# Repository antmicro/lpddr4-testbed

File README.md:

LPDDR4 testbed
==============

Copyright (c) 2020-2025 [Antmicro](https://www.antmicro.com)

Overview
--------

This repository contains open hardware design files for an experimental
test module in a form of SO-DIMM DDR4 module. The module includes a
standard 200-ball WFBGA (10mm × 14.5mm × 0.8mm, Ø0.35 SMD) LPDDR4 RAM
footprint break-routed in the SO-DOMM edge connector. The design files
were prepared in KiCad. Please note that this board is not electrically
compatible with off-the-shelf SO-DIMM DDR4 memory modules. It is
compatible with [this](https://github.com/antmicro/lpddr4-test-board)
LPDDR4 test platform.

Repository structure
--------------------

The main repository directory contains KiCad PCB project files, a
LICENSE and README. The remaining files are stored in the following
directories:

* `img` - contains graphics for this README

### Licensing

This project is published under the [Apache-2.0](LICENSE) license.

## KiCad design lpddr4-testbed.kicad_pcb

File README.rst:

==============
LPDDR4 testbed
==============

Copyright (c) 2020-2021 `Antmicro <https://www.antmicro.com>`_

.. figure:: img/lpddr4-testbed.jpg

Overview
--------

This repository contains open hardware design files for an experimental test module in a form of SO-DIMM DDR4 module. The module includes a standard 200-ball WFBGA (10mm × 14.5mm ×
0.8mm, Ø0.35 SMD) LPDDR4 RAM footprint break-routed in the SO-DOMM edge connector.
The design files were prepared in KiCad.
Please note that this board is not electrically compatible with off-the-shelf SO-DIMM DDR4 memory modules.
It is compatible with `this <https://github.com/antmicro/lpddr4-test-board>`_ LPDDR4 test platform.

Repository structure
--------------------
The main repository directory contains KiCad PCB project files, a LICENSE and README.
The remaining files are stored in the following directories:

* ``lib`` - contains the component libraries
* ``img`` - contains graphics for this README

License
=======

`Apache-2.0 <LICENSE>`_

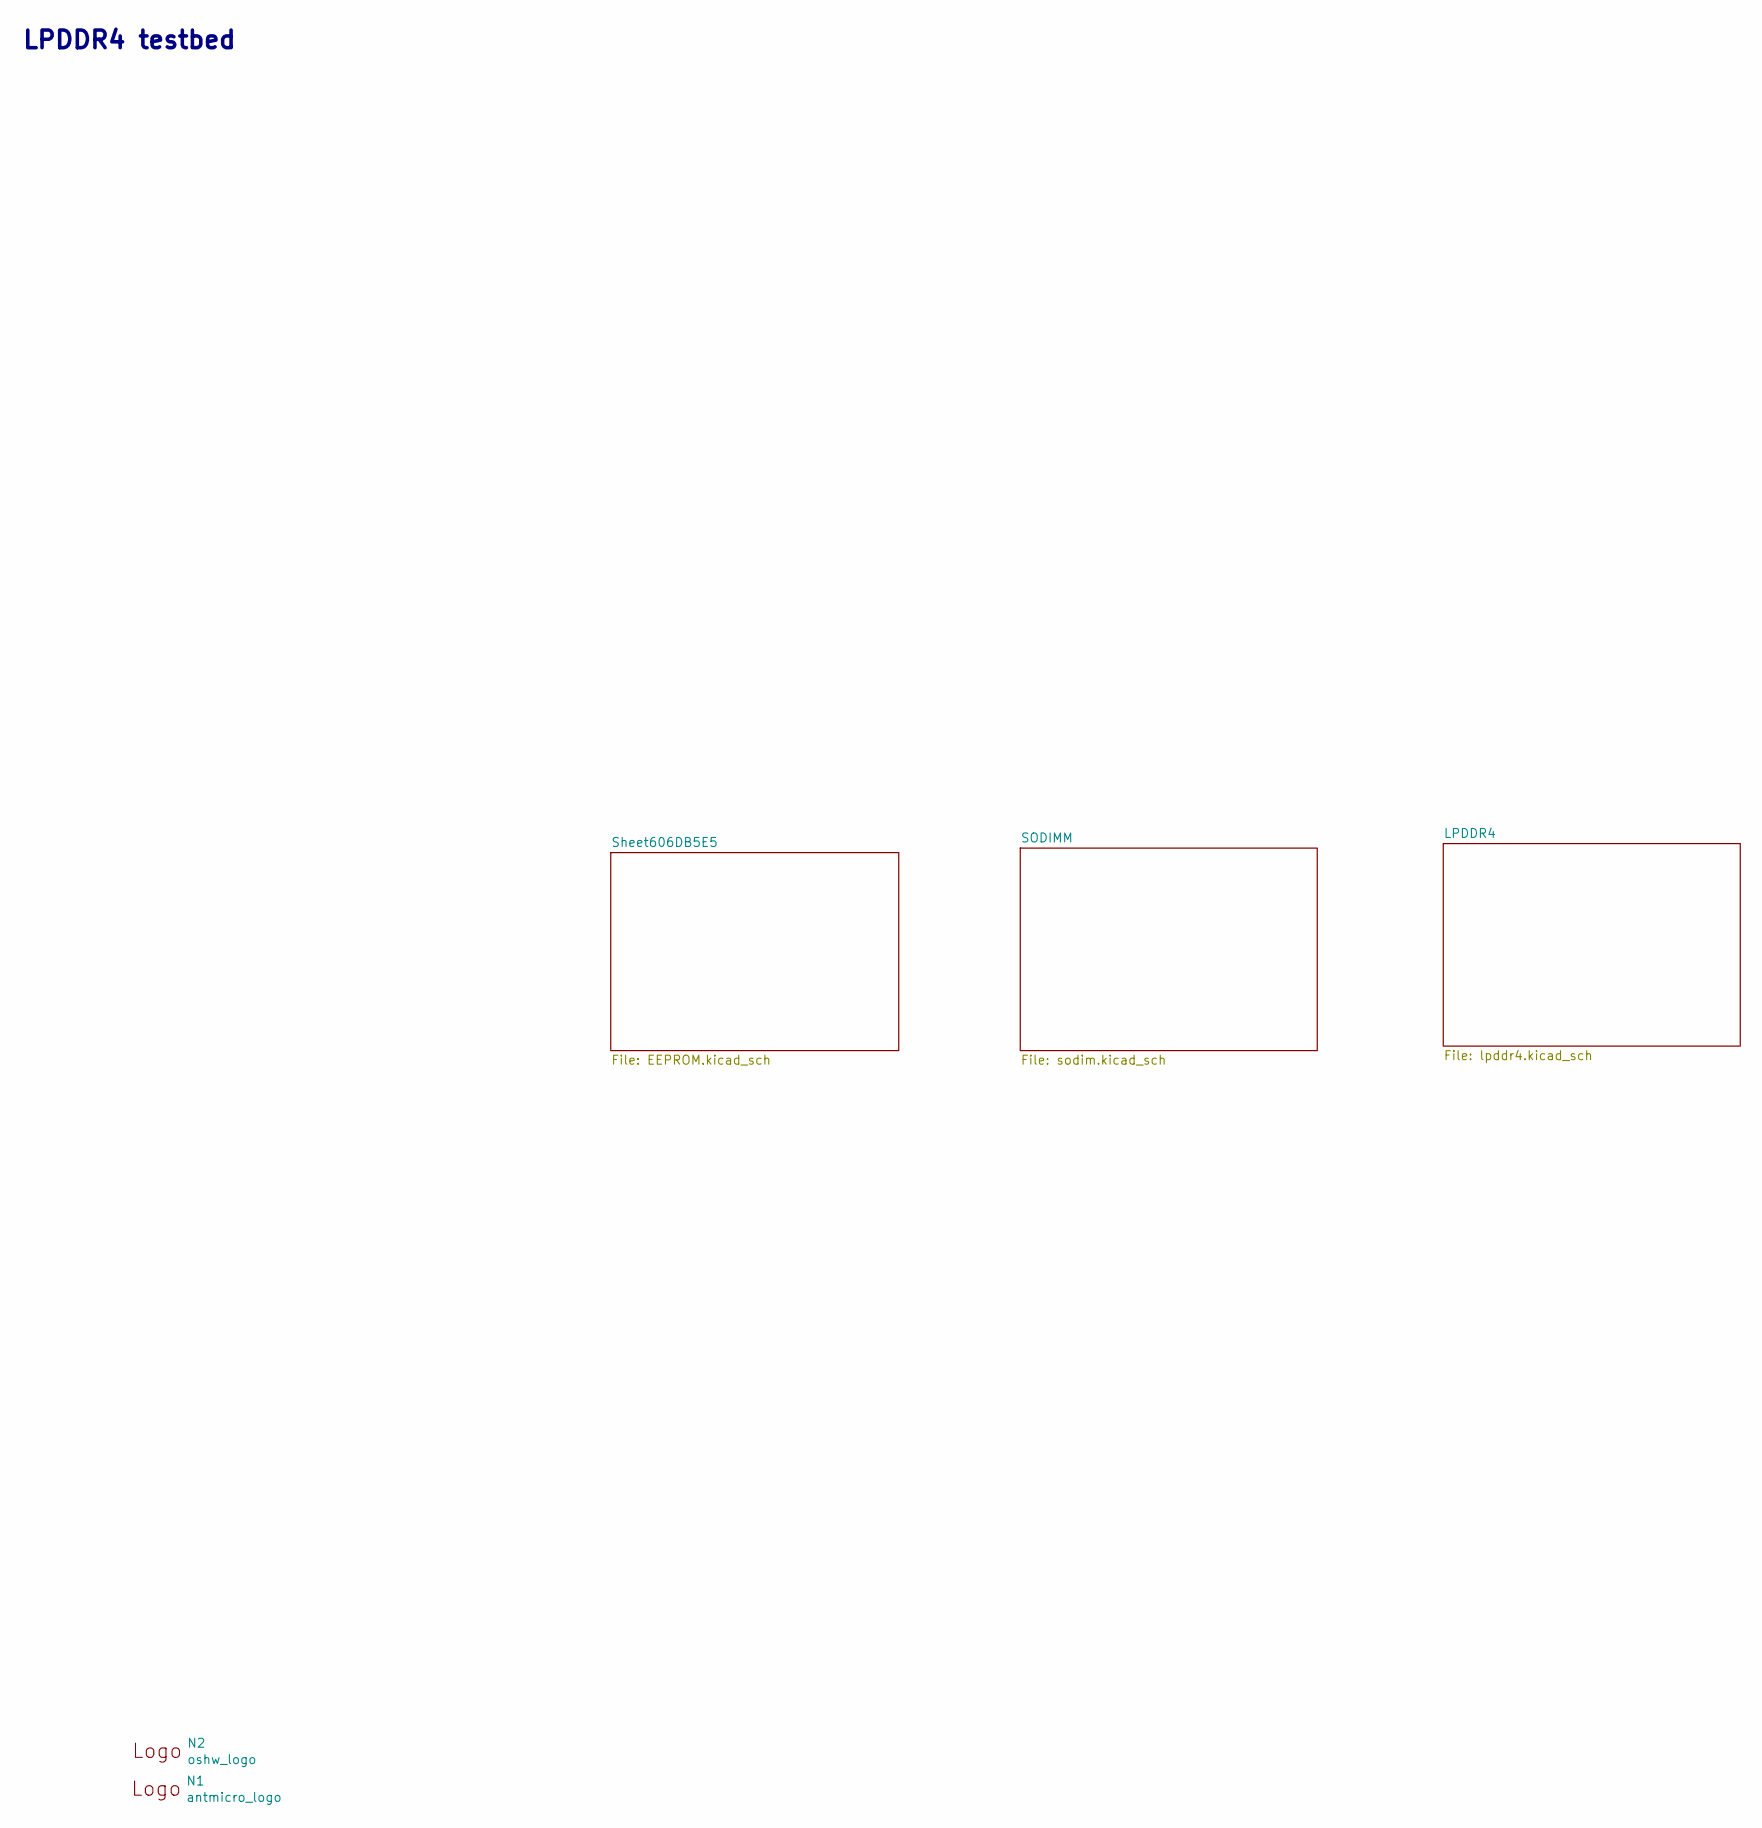
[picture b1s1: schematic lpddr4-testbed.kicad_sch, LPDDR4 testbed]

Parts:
N1: antmicro_logo; antmicro-logo_scaled_20mm
N2: oshw_logo; oshw-logo

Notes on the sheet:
LPDDR4 testbed

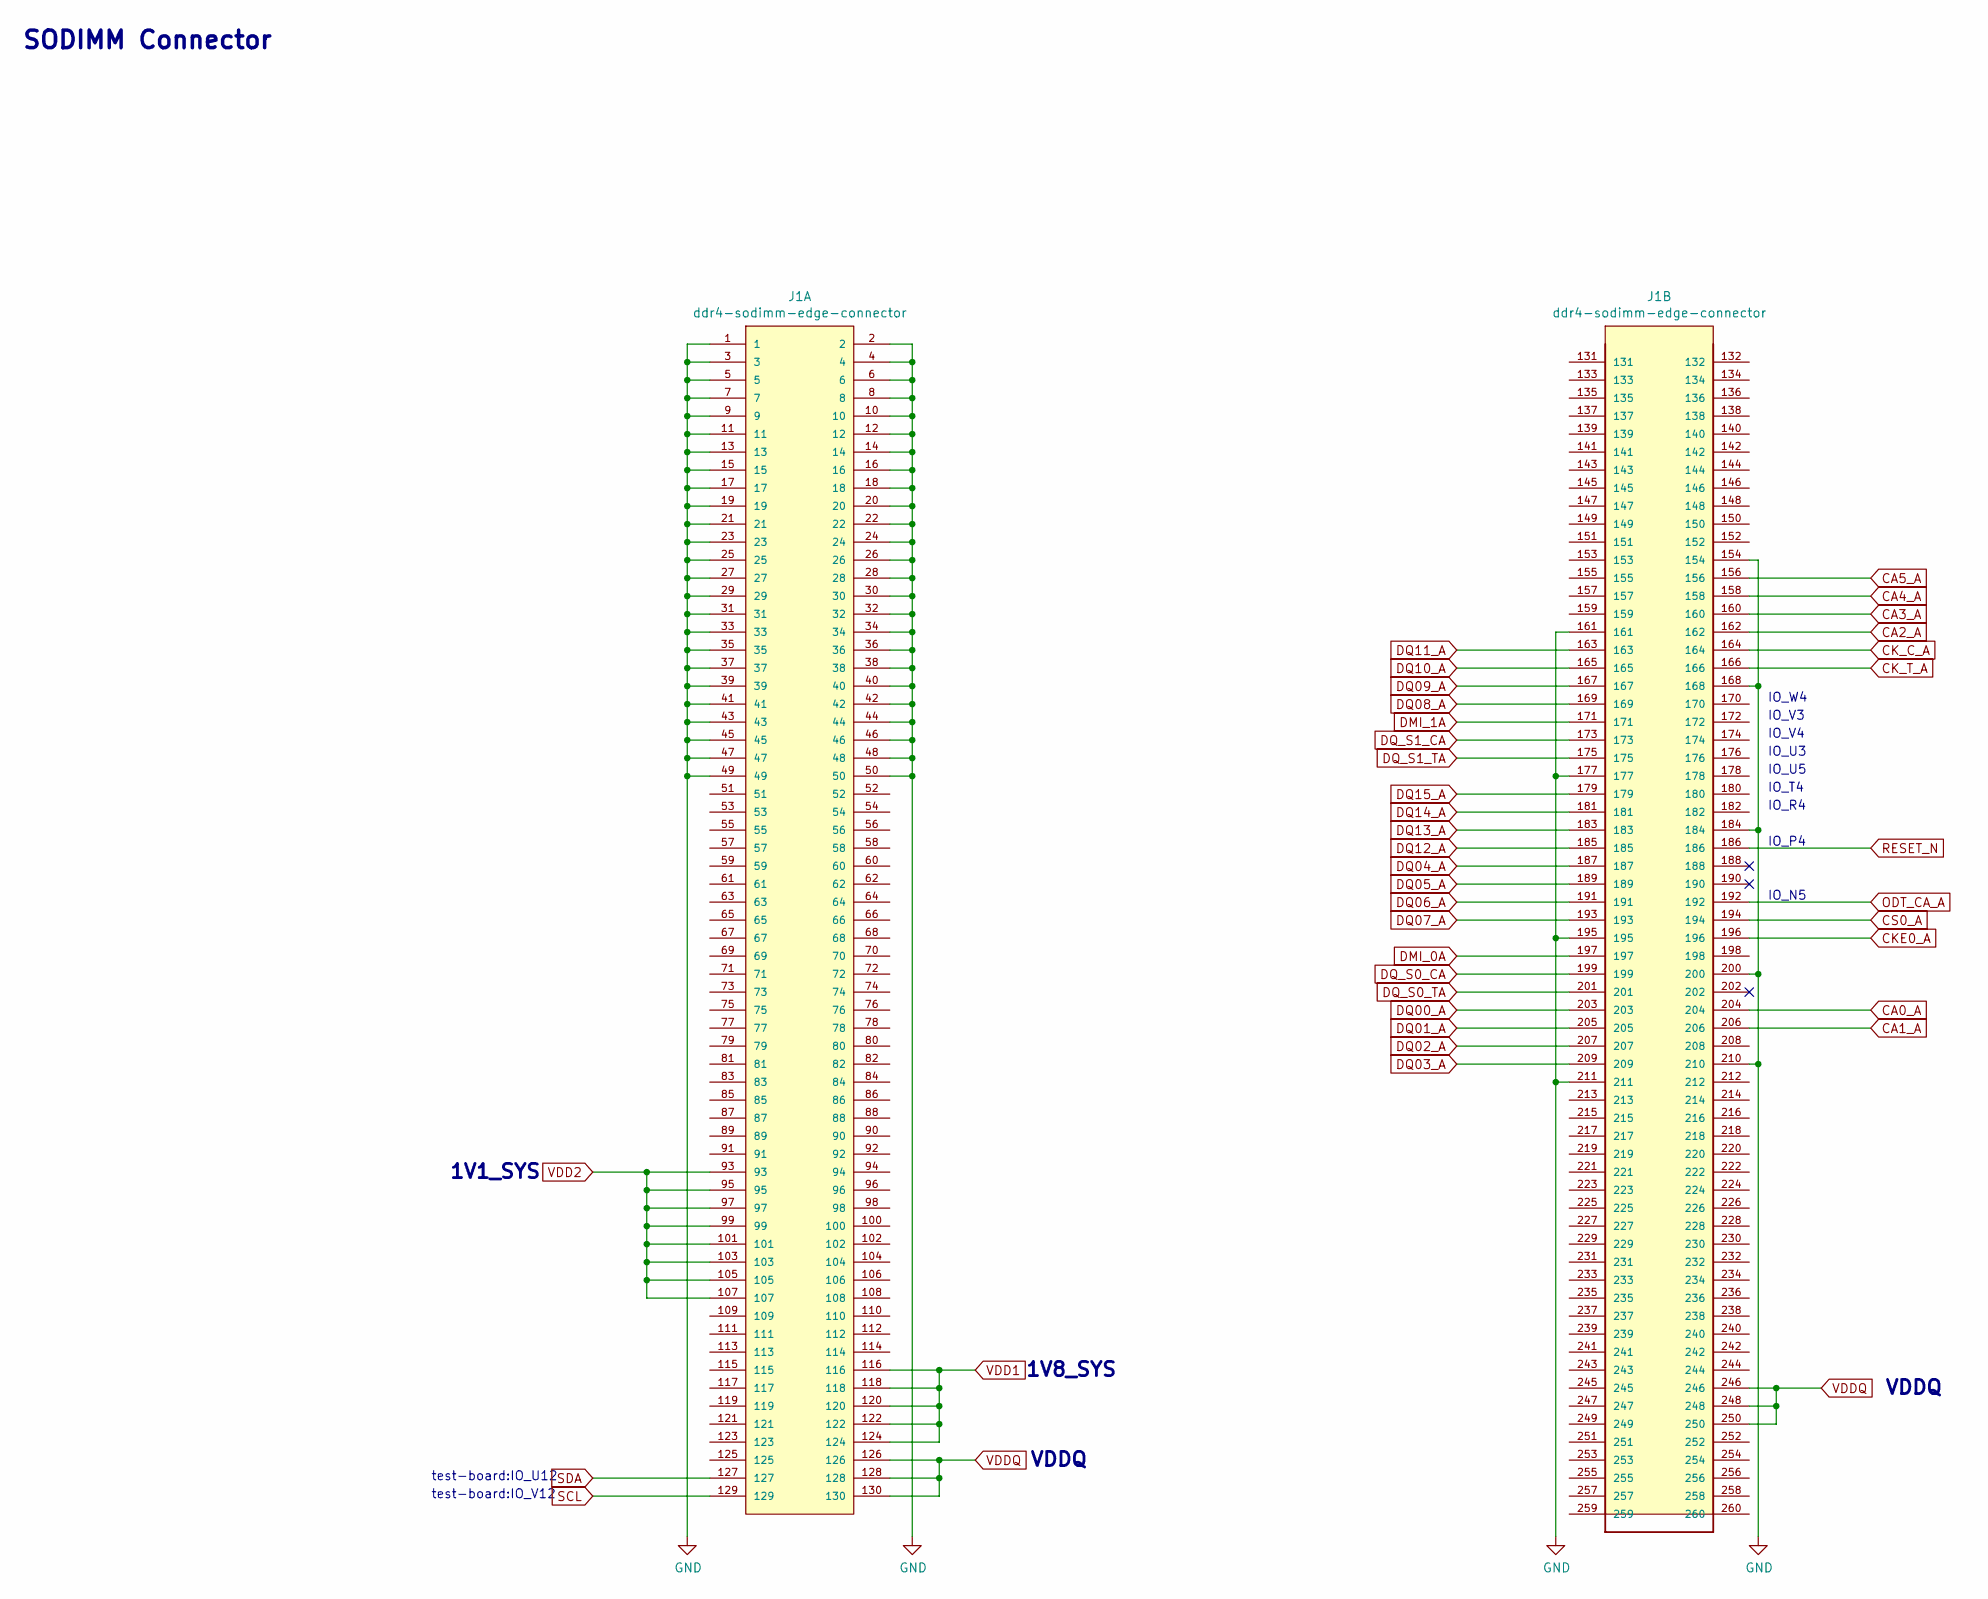
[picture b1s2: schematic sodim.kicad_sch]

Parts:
J1: ddr4-sodimm-edge-connector; SODIMM_DDR4_EDGE

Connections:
CA0_A: J1.204; also elsewhere on the board
CA1_A: J1.206; also elsewhere on the board
CA2_A: J1.162; also elsewhere on the board
CA3_A: J1.160; also elsewhere on the board
CA4_A: J1.158; also elsewhere on the board
CA5_A: J1.156; also elsewhere on the board
CKE0_A: J1.196; also elsewhere on the board
CK_C_A: J1.164; also elsewhere on the board
CK_T_A: J1.166; also elsewhere on the board
CS0_A: J1.194; also elsewhere on the board
DMI_0A: J1.197; also elsewhere on the board
DMI_1A: J1.171; also elsewhere on the board
DQ00_A: J1.203; also elsewhere on the board
DQ01_A: J1.205; also elsewhere on the board
DQ02_A: J1.207; also elsewhere on the board
DQ03_A: J1.209; also elsewhere on the board
DQ04_A: J1.187; also elsewhere on the board
DQ05_A: J1.189; also elsewhere on the board
DQ06_A: J1.191; also elsewhere on the board
DQ07_A: J1.193; also elsewhere on the board
DQ08_A: J1.169; also elsewhere on the board
DQ09_A: J1.167; also elsewhere on the board
DQ10_A: J1.165; also elsewhere on the board
DQ11_A: J1.163; also elsewhere on the board
DQ12_A: J1.185; also elsewhere on the board
DQ13_A: J1.183; also elsewhere on the board
DQ14_A: J1.181; also elsewhere on the board
DQ15_A: J1.179; also elsewhere on the board
DQ_S0_CA: J1.199; also elsewhere on the board
DQ_S0_TA: J1.201; also elsewhere on the board
DQ_S1_CA: J1.173; also elsewhere on the board
DQ_S1_TA: J1.175; also elsewhere on the board
GND: J1.1, J1.2, J1.3, J1.4, J1.5, J1.6, J1.7, J1.8, J1.9, J1.10, J1.11, J1.12, J1.13, J1.14, J1.15, J1.16, J1.17, J1.18, J1.19, J1.20, J1.21, J1.22, J1.23, J1.24, J1.25, J1.26, J1.27, J1.28, J1.29, J1.30, J1.31, J1.32, J1.33, J1.34, J1.35, J1.36, J1.37, J1.38, J1.39, J1.40, J1.41, J1.42, J1.43, J1.44, J1.45, J1.46, J1.47, J1.48, J1.49, J1.50, J1.154, J1.161, J1.168, J1.177, J1.184, J1.195, J1.200, J1.210, J1.211; also elsewhere on the board
ODT_CA_A: J1.192; also elsewhere on the board
RESET_N: J1.186; also elsewhere on the board
SCL: J1.129; also elsewhere on the board
SDA: J1.127; also elsewhere on the board
VDD1: J1.116, J1.118, J1.120, J1.122, J1.124; also elsewhere on the board
VDD2: J1.93, J1.95, J1.97, J1.99, J1.101, J1.103, J1.105, J1.107; also elsewhere on the board
VDDQ: J1.126, J1.128, J1.130, J1.246, J1.248, J1.250; also elsewhere on the board

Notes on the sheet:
IO_W4
IO_N5
IO_U5
IO_T4
test-board:IO_U12
VDDQ
IO_U3
IO_V4
IO_P4
test-board:IO_V12
SODIMM Connector
IO_V3
IO_R4
1V8_SYS
1V1_SYS

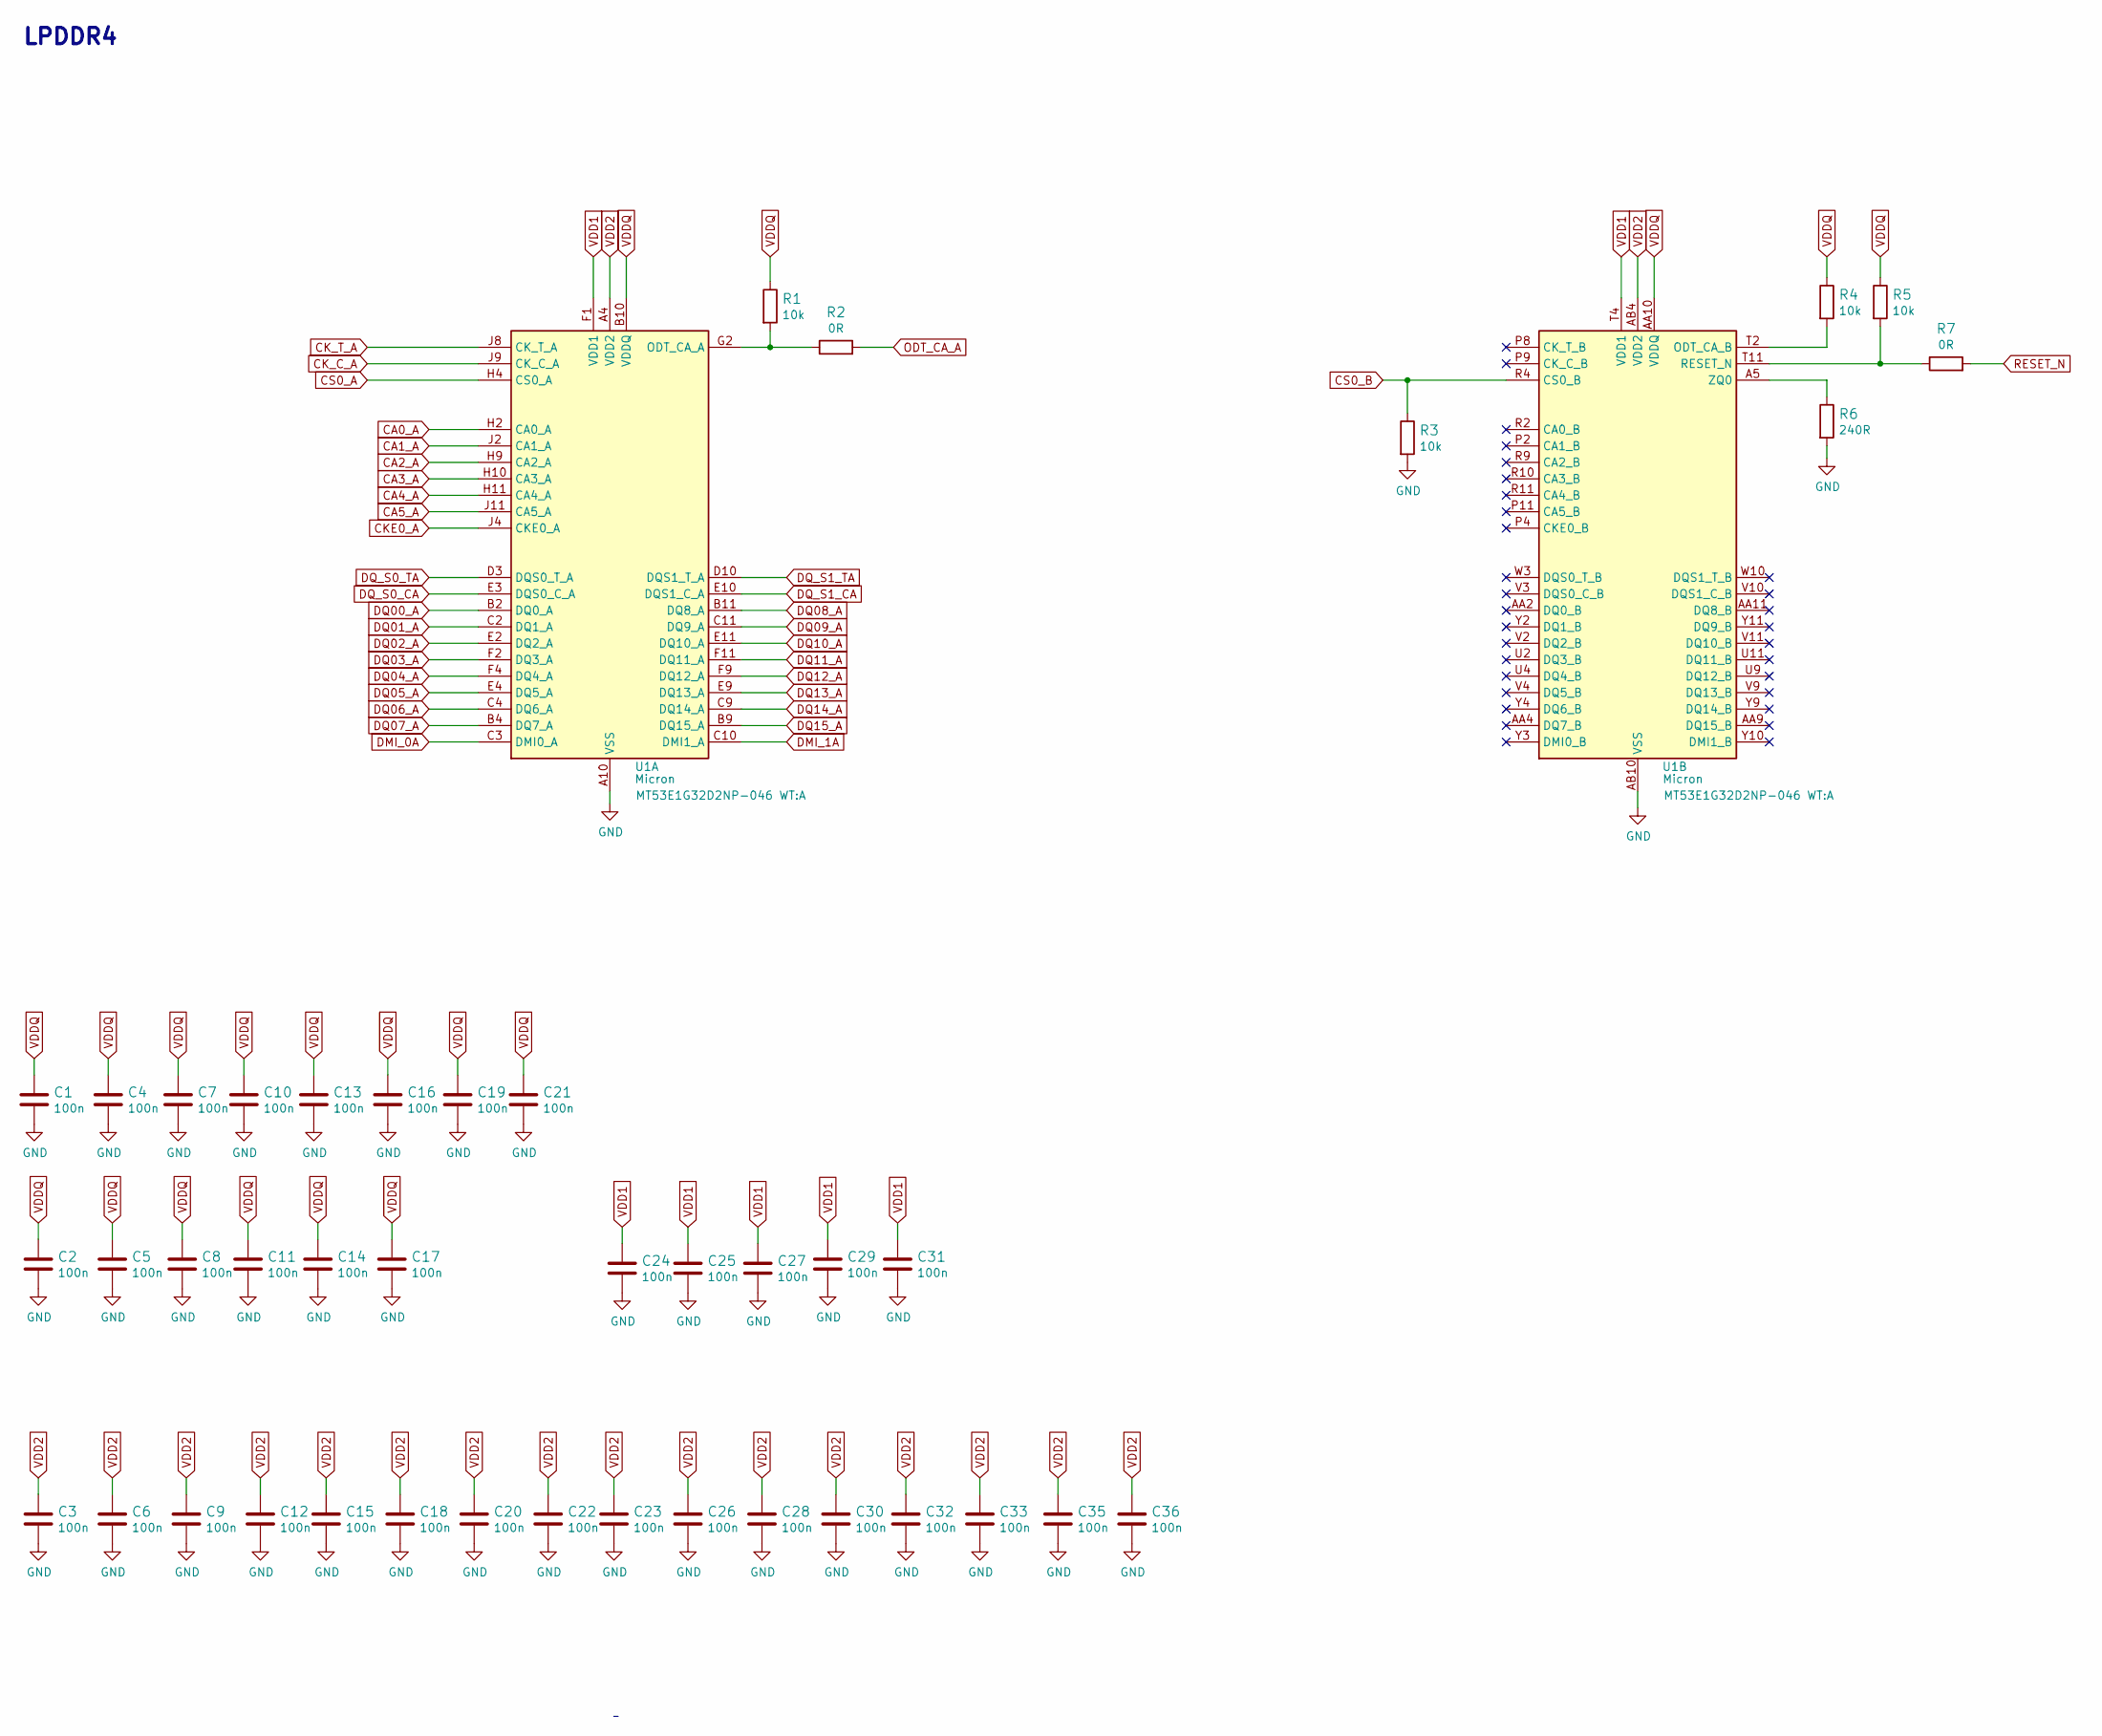
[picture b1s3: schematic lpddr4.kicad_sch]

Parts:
C1, C2, C3, C4, C5, C6, C7, C8, C9, C10, C11, C12, C13, C14, C15, C16, C17, C18, C19, C20, C21, C22, C23, C24, C25, C26, C27, C28, C29, C30, C31, C32, C33, C35, C36: C_100n_0201; 0201-res; MPN CC0201KRX6S5BB104
R1, R3, R4, R5: R_10k_0402; 0402-res; MPN CRCW040210K0FKEDHP
R2, R7: R_0R_0402; 0402-res; MPN ERJ2GE0R00X
R6: R_240R_0402; 0402-res; MPN ERJ2GEJ241X
U1: MT53E1G32D2NP-046; BGA-200_10.0x14.5mm_Layout12x22_P0.80x0.65mm; MPN MT53E1G32D2NP-046 WT:A

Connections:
CA0_A: U1.H2 (CA0_A); also elsewhere on the board
CA1_A: U1.J2 (CA1_A); also elsewhere on the board
CA2_A: U1.H9 (CA2_A); also elsewhere on the board
CA3_A: U1.H10 (CA3_A); also elsewhere on the board
CA4_A: U1.H11 (CA4_A); also elsewhere on the board
CA5_A: U1.J11 (CA5_A); also elsewhere on the board
CKE0_A: U1.J4 (CKE0_A); also elsewhere on the board
CK_C_A: U1.J9 (CK_C_A); also elsewhere on the board
CK_T_A: U1.J8 (CK_T_A); also elsewhere on the board
CS0_A: U1.H4 (CS0_A); also elsewhere on the board
CS0_B: R3.1, U1.R4 (CS0_B)
DMI_0A: U1.C3 (DMI0_A); also elsewhere on the board
DMI_1A: U1.C10 (DMI1_A); also elsewhere on the board
DQ00_A: U1.B2 (DQ0_A); also elsewhere on the board
DQ01_A: U1.C2 (DQ1_A); also elsewhere on the board
DQ02_A: U1.E2 (DQ2_A); also elsewhere on the board
DQ03_A: U1.F2 (DQ3_A); also elsewhere on the board
DQ04_A: U1.F4 (DQ4_A); also elsewhere on the board
DQ05_A: U1.E4 (DQ5_A); also elsewhere on the board
DQ06_A: U1.C4 (DQ6_A); also elsewhere on the board
DQ07_A: U1.B4 (DQ7_A); also elsewhere on the board
DQ08_A: U1.B11 (DQ8_A); also elsewhere on the board
DQ09_A: U1.C11 (DQ9_A); also elsewhere on the board
DQ10_A: U1.E11 (DQ10_A); also elsewhere on the board
DQ11_A: U1.F11 (DQ11_A); also elsewhere on the board
DQ12_A: U1.F9 (DQ12_A); also elsewhere on the board
DQ13_A: U1.E9 (DQ13_A); also elsewhere on the board
DQ14_A: U1.C9 (DQ14_A); also elsewhere on the board
DQ15_A: U1.B9 (DQ15_A); also elsewhere on the board
DQ_S0_CA: U1.E3 (DQS0_C_A); also elsewhere on the board
DQ_S0_TA: U1.D3 (DQS0_T_A); also elsewhere on the board
DQ_S1_CA: U1.E10 (DQS1_C_A); also elsewhere on the board
DQ_S1_TA: U1.D10 (DQS1_T_A); also elsewhere on the board
GND: C1.2, C2.2, C3.2, C4.2, C5.2, C6.2, C7.2, C8.2, C9.2, C10.2, C11.2, C12.2, C13.2, C14.2, C15.2, C16.2, C17.2, C18.2, C19.2, C20.2, C21.2, C22.2, C23.2, C24.2, C25.2, C26.2, C27.2, C28.2, C29.2, C30.2, C31.2, C32.2, C33.2, C35.2, C36.2, R3.2, R6.2, U1.A3 (VSS), U1.A10 (VSS), U1.AB3 (VSS), U1.AB5 (VSS), U1.AB8 (VSS), U1.AB10 (VSS), U1.C1 (VSS), U1.C5 (VSS), U1.C8 (VSS), U1.C12 (VSS), U1.D2 (VSS), U1.D4 (VSS), U1.D9 (VSS), U1.D11 (VSS), U1.E1 (VSS), U1.E5 (VSS), U1.E8 (VSS), U1.E12 (VSS), U1.G1 (VSS), U1.G3 (VSS), U1.G5 (VSS), U1.G8 (VSS), U1.G10 (VSS), U1.G12 (VSS), U1.J1 (VSS), U1.J3 (VSS), U1.J10 (VSS), U1.J12 (VSS), U1.K2 (VSS), U1.K4 (VSS), U1.K9 (VSS), U1.K11 (VSS), U1.N2 (VSS), U1.N4 (VSS), U1.N9 (VSS), U1.N11 (VSS), U1.P1 (VSS), U1.P3 (VSS), U1.P10 (VSS), U1.P12 (VSS), U1.T1 (VSS), U1.T3 (VSS), U1.T5 (VSS), U1.T8 (VSS), U1.T10 (VSS), U1.T12 (VSS), U1.V1 (VSS), U1.V5 (VSS), U1.V8 (VSS), U1.V12 (VSS), U1.W2 (VSS), U1.W4 (VSS), U1.W9 (VSS), U1.W11 (VSS), U1.Y1 (VSS), U1.Y5 (VSS), U1.Y8 (VSS), U1.Y12 (VSS); also elsewhere on the board
unnamed: R1.2, R2.1, U1.G2 (ODT_CA_A)
unnamed: R4.2, U1.T2 (ODT_CA_B)
unnamed: R5.2, R7.1, U1.T11 (RESET_N)
unnamed: R6.1, U1.A5 (ZQ0)
ODT_CA_A: R2.2; also elsewhere on the board
RESET_N: R7.2; also elsewhere on the board
VDD1: C24.1, C25.1, C27.1, C29.1, C31.1, U1.F1 (VDD1), U1.F12 (VDD1), U1.G4 (VDD1), U1.G9 (VDD1), U1.T4 (VDD1), U1.T9 (VDD1), U1.U1 (VDD1), U1.U12 (VDD1); also elsewhere on the board
VDD2: C3.1, C6.1, C9.1, C12.1, C15.1, C18.1, C20.1, C22.1, C23.1, C26.1, C28.1, C30.1, C32.1, C33.1, C35.1, C36.1, U1.A4 (VDD2), U1.A9 (VDD2), U1.AB4 (VDD2), U1.AB9 (VDD2), U1.F5 (VDD2), U1.F8 (VDD2), U1.H1 (VDD2), U1.H5 (VDD2), U1.H8 (VDD2), U1.H12 (VDD2), U1.K1 (VDD2), U1.K3 (VDD2), U1.K10 (VDD2), U1.K12 (VDD2), U1.N1 (VDD2), U1.N3 (VDD2), U1.N10 (VDD2), U1.N12 (VDD2), U1.R1 (VDD2), U1.R5 (VDD2), U1.R8 (VDD2), U1.R12 (VDD2), U1.U5 (VDD2), U1.U8 (VDD2); also elsewhere on the board
VDDQ: C1.1, C2.1, C4.1, C5.1, C7.1, C8.1, C10.1, C11.1, C13.1, C14.1, C16.1, C17.1, C19.1, C21.1, R1.1, R4.1, R5.1, U1.AA3 (VDDQ), U1.AA5 (VDDQ), U1.AA8 (VDDQ), U1.AA10 (VDDQ), U1.B3 (VDDQ), U1.B5 (VDDQ), U1.B8 (VDDQ), U1.B10 (VDDQ), U1.D1 (VDDQ), U1.D5 (VDDQ), U1.D8 (VDDQ), U1.D12 (VDDQ), U1.F3 (VDDQ), U1.F10 (VDDQ), U1.U3 (VDDQ), U1.U10 (VDDQ), U1.W1 (VDDQ), U1.W5 (VDDQ), U1.W8 (VDDQ), U1.W12 (VDDQ); also elsewhere on the board

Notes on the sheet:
LPDDR4

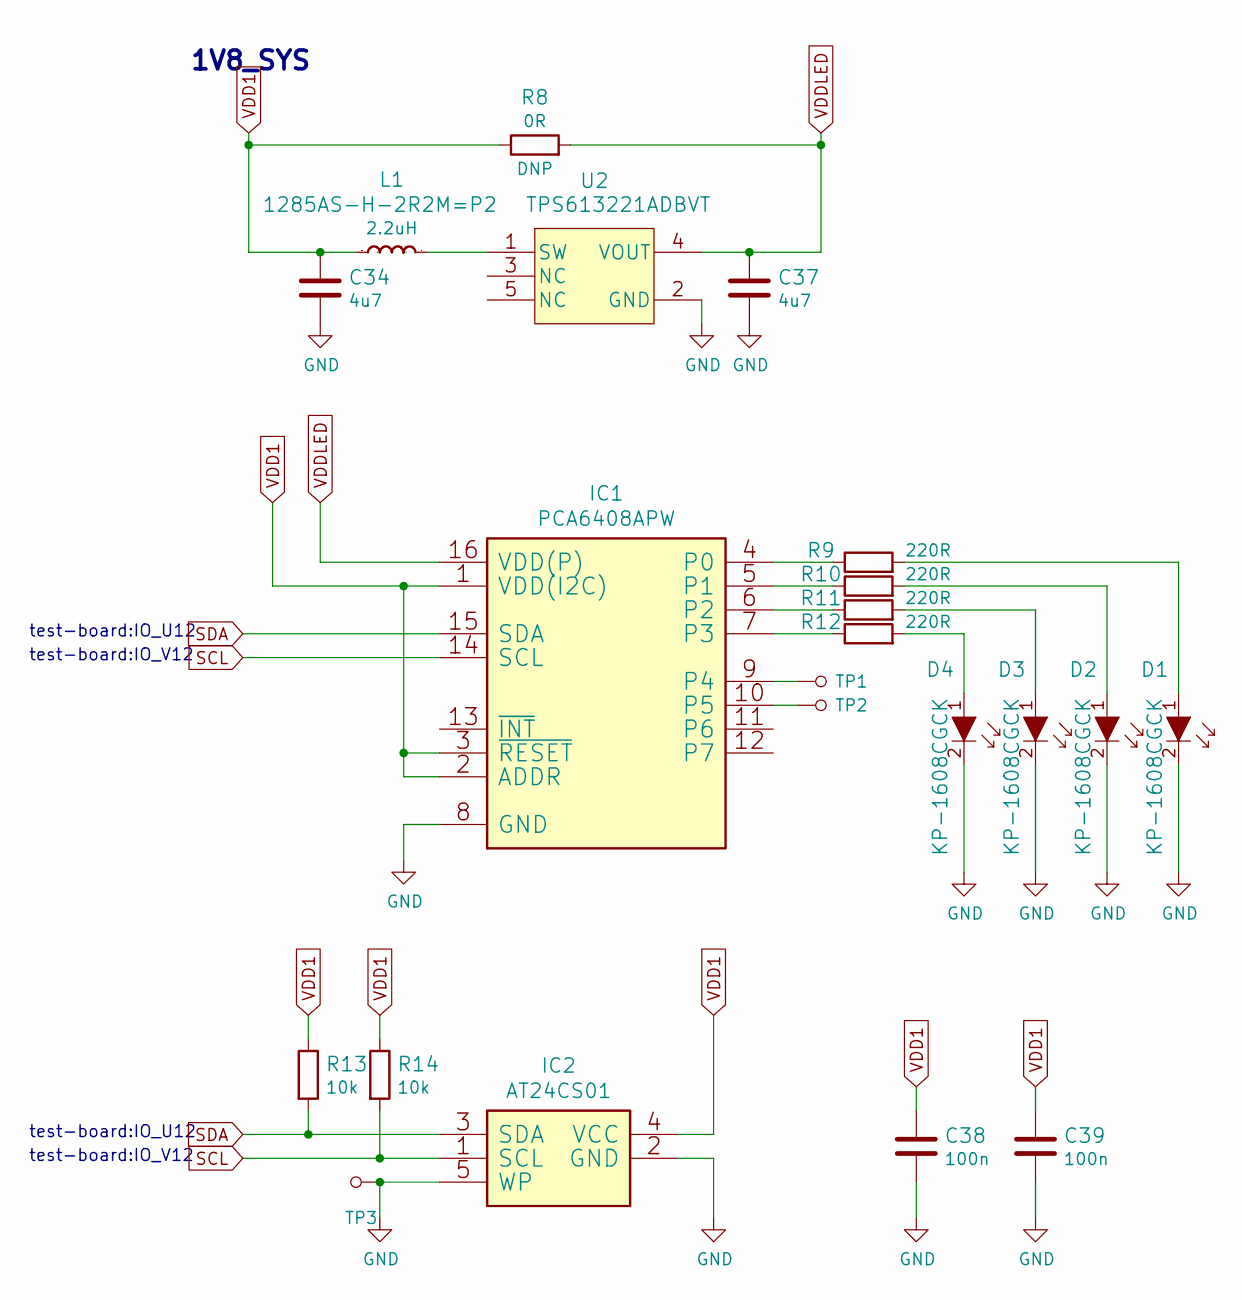
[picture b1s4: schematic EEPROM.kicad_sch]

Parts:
C34, C37: C_4u7_0402; 0402-cap; MPN GRM155R61A475MEAAD
C38, C39: C_100n_0402; 0402-cap; MPN 0402X104K6R3CT
D1, D2, D3, D4: KP-1608CGCK; LED_0603; MPN KP-1608CGCK
IC1: PCA6408APW; TSSOP-16; MPN PCA6408APW
IC2: AT24CS01; SOT-23-5; MPN AT24CS01-ST
L1: 1285AS-H-2R2M=P2; 0805-res; MPN 1285AS-H-2R2M=P2
R8: R_0R_0402; 0402-res; MPN ERJ2GE0R00X
R9, R10, R11, R12: R_220R_0402; 0402-res; MPN ERJ2GEJ221X
R13, R14: R_10k_0402; 0402-res; MPN CRCW040210K0FKEDHP
TP1, TP2, TP3: TP_SMD1MM; Testpoint_smd_1mm
U2: TPS613221ADBVT; SOT-23-5; MPN TPS613221ADBVT

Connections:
GND: C34.2, C37.2, C38.2, C39.2, D1.2, D2.2, D3.2, D4.2, IC1.8 (GND), IC2.2 (GND), IC2.5 (WP), TP3.1, U2.2 (GND); also elsewhere on the board
unnamed: D1.1, R9.2
unnamed: D2.1, R10.2
unnamed: D3.1, R11.2
unnamed: D4.1, R12.2
unnamed: IC1.4 (P0), R9.1
unnamed: IC1.5 (P1), R10.1
unnamed: IC1.6 (P2), R11.1
unnamed: IC1.7 (P3), R12.1
unnamed: IC1.9 (P4), TP1.1
unnamed: IC1.10 (P5), TP2.1
unnamed: L1.2, U2.1 (SW)
SCL: IC1.14 (SCL), IC2.1 (SCL), R14.2; also elsewhere on the board
SDA: IC1.15 (SDA), IC2.3 (SDA), R13.2; also elsewhere on the board
VDD1: C34.1, C38.1, C39.1, IC1.1 (VDD(I2C)), IC1.2 (ADDR), IC1.3 (~RESET), IC2.4 (VCC), L1.1, R8.1, R13.1, R14.1; also elsewhere on the board
VDDLED: C37.1, IC1.16 (VDD(P)), R8.2, U2.4 (VOUT)

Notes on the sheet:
test-board:IO_V12
test-board:IO_U12
1V8_SYS

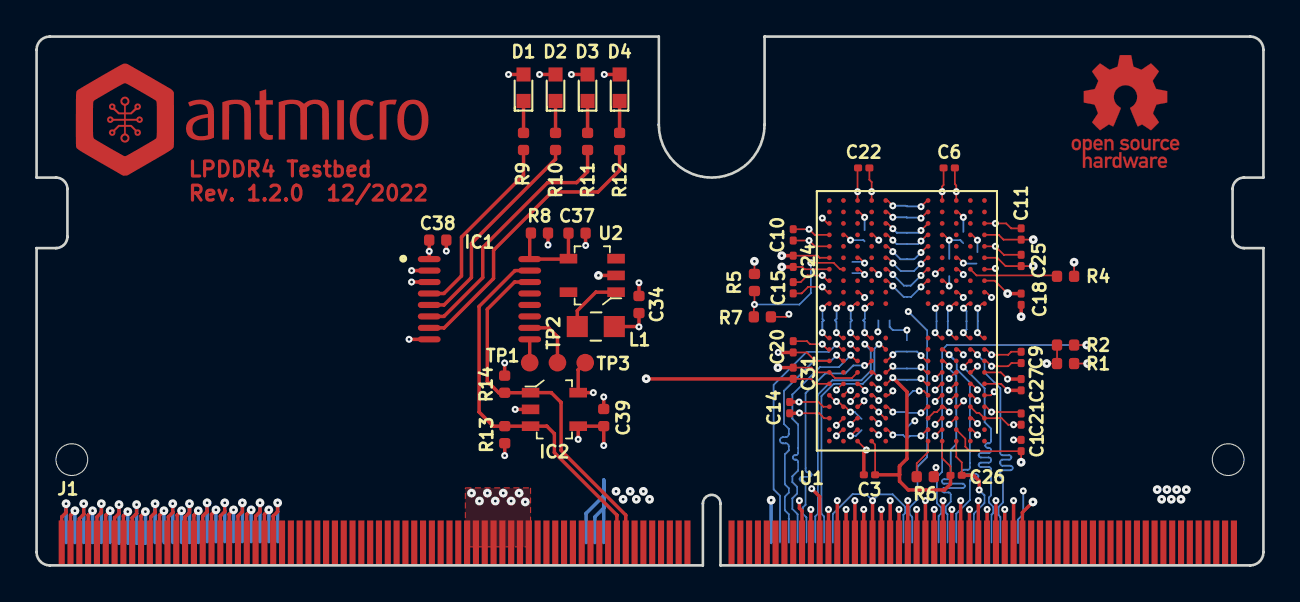
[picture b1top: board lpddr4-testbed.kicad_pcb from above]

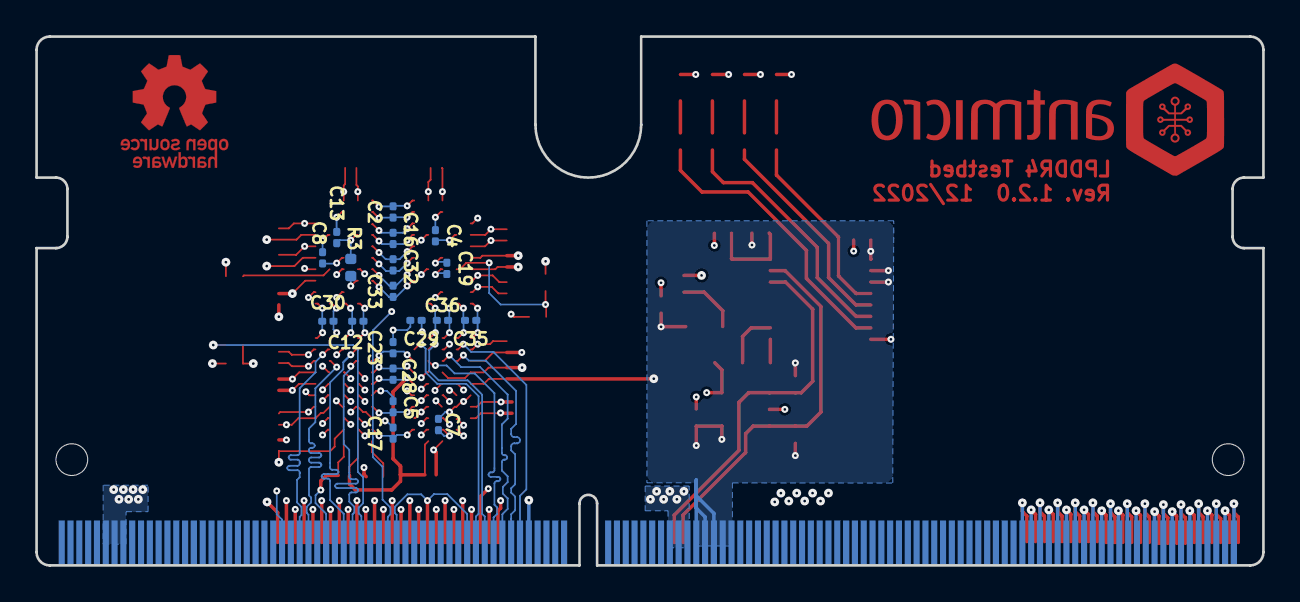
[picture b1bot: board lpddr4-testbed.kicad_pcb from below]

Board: 6 copper layers, 69.6 x 30.0 mm, 68 parts (19 on the bottom side), 57 nets.

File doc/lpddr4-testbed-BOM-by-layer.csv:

Reference,Quantity,Value,Footprint,Manufacturer,MPN,Layer,
C1 C3 C6 C9 C10 C11 C14 C15 C18 C20 C21 C22 C24 C25 C26 C27 C31,17,C_100n_0201,0201-res,YAGEO,CC0201KRX6S5BB104,Top,
J1 J1,2,ddr4-sodimm-edge-connector,SODIMM_DDR4_EDGE,,,Top,
R1 R4 R5,3,R_10k_0402,0402-res,VISHAY,CRCW040210K0FKEDHP,Top,
R2 R7,2,R_0R_0402,0402-res,PANASONIC,ERJ2GE0R00X,Top,
R6,1,R_240R_0402,0402-res,PANASONIC,ERJ2GEJ241X,Top,
U1 U1,2,MT53E256M32D2DS-053,BGA-200_10.0x14.5mm_Layout12x22_P0.80x0.65mm,Micron,MT53E256M32D2DS-053 WT:B,Top,
C2 C4 C5 C7 C8 C12 C13 C16 C17 C19 C23 C28 C29 C30 C32 C33 C35 C36,18,C_100n_0201,0201-res,YAGEO,CC0201KRX6S5BB104,Bottom,
R3,1,R_10k_0402,0402-res,VISHAY,CRCW040210K0FKEDHP,Bottom,
N1,1,antmicro_logo,antmicro-logo,,,Virtual,
N2,1,oshw_logo,oshw-logo,,,Virtual,
N3,1,oshw_logo,oshw-logo,,,Unknown,
